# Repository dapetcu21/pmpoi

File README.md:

# PM Poi

> Visual Poi hardware project.

## Definitions

[Poi - performance art, Wikipedia page](https://en.wikipedia.org/wiki/Poi_(performance_art)#Glow_poi.2Fglowstringing)

It looks like this:

## About this project

This is my project for the MCU programming class from University.

## Hardware

Since this is a project for Uni, we had to use the provided ATMEGA324PA development [board](./hardware/pm2016.brd).

On top of it, I created an extension [board](./hardware/pmpoi.sch) with a shield-like form factor.

The main stars of the extension board are:

  * 8 RGB LEDs connected to the entirety of PORTB, PORTD and PORTA through a set of transitor array ICs. I could have used some PWM driver IC, but then where's all the fun? (To be read as: I didn't want to wait for the parts, so I just used what I could readily find at my local vendor.)

  * an MPU6050 gyro (on a GY-521 breakout board).

  * 3 buttons for good measure.

  * 3 AAA batteries to keep the board running.

Since this will spin freely in the air, I needed to make it sturdy, so I used screw mount dividers and no ribbon cables for the build.

Of course, most poi tehnique requires two poi, so I had to make two.

Attach this to a set of poi leashes and we're ready to dance.

### Caveats

Since I configured my bootloader to start when PD7 is pressed (sunk to GND) and I also connected PD7 to the input of the transistor array (which also pulled to GND, probably in a more stronger fashion than the 20K internal pull-up on PD7 protects against), I had to add a stronger pull-up resistor on that pin (3.3K).

Of course, since I also had to use PD2 and PD3 for the LEDs, plugging this into a computer won't do anything. But then if you want to program it, sometimes a reset is not be enough for your computer to pick it up. You might have to unplug the cable, wait a few seconds and plug it again. This happens because your computer's USB controller remembers that a non-compliant USB device was plugged into that port and decides to ignore it, even if you decide to send valid USB traffic at some point.

## Software

For the bootloader, I used [USBaspLoader](https://github.com/baerwolf/USBaspLoader) since it works via V-USB and plays nice with avrdude.

As a development environment, I just wrote a `Makefile` and a `.clang_complete` file to get autocomplete to work and built the whole thing in Atom.

### LED PWM

Since I have to drive 8 RGB LEDs (24 independent channels) in software PWM operation, I decided to use a novel approach:

Since PWM has to be fast, we have to keep our timer's ISR small.

I decided to use all the pins from 3 ports because it's easy to change them all at the same time. That's why, every time I would need to change the color of the LEDs, I would pre-calculate a render buffer with `B[i]`, the state of the each of the 3 ports at the time `i`. We can make `i` sweep from `0` to `15` and then loop around as the timer ticks.

For example, let's say I want to keep one of the LEDs at 25% brightness. I would first figure out what's the corresponding port and bit for the LED, then mark it as `1` in `B[0]`, `B[1]`, `B[2]`, `B[3]` and as `0` in `B[4- 15]`. This way, as the timer sweeps the render buffer, the LED will be lit 4 times out of 16.

Because modifying the render buffer during rendering might cause unexpected flickers, I decided to go with a double buffered approach. Every time I need to update the color of the LEDs, I fill in an off-screen render buffer, then mark it as ready for display. The ISR would then swap it with its current render buffer at the end of a `0 - 16` cycle (frame).

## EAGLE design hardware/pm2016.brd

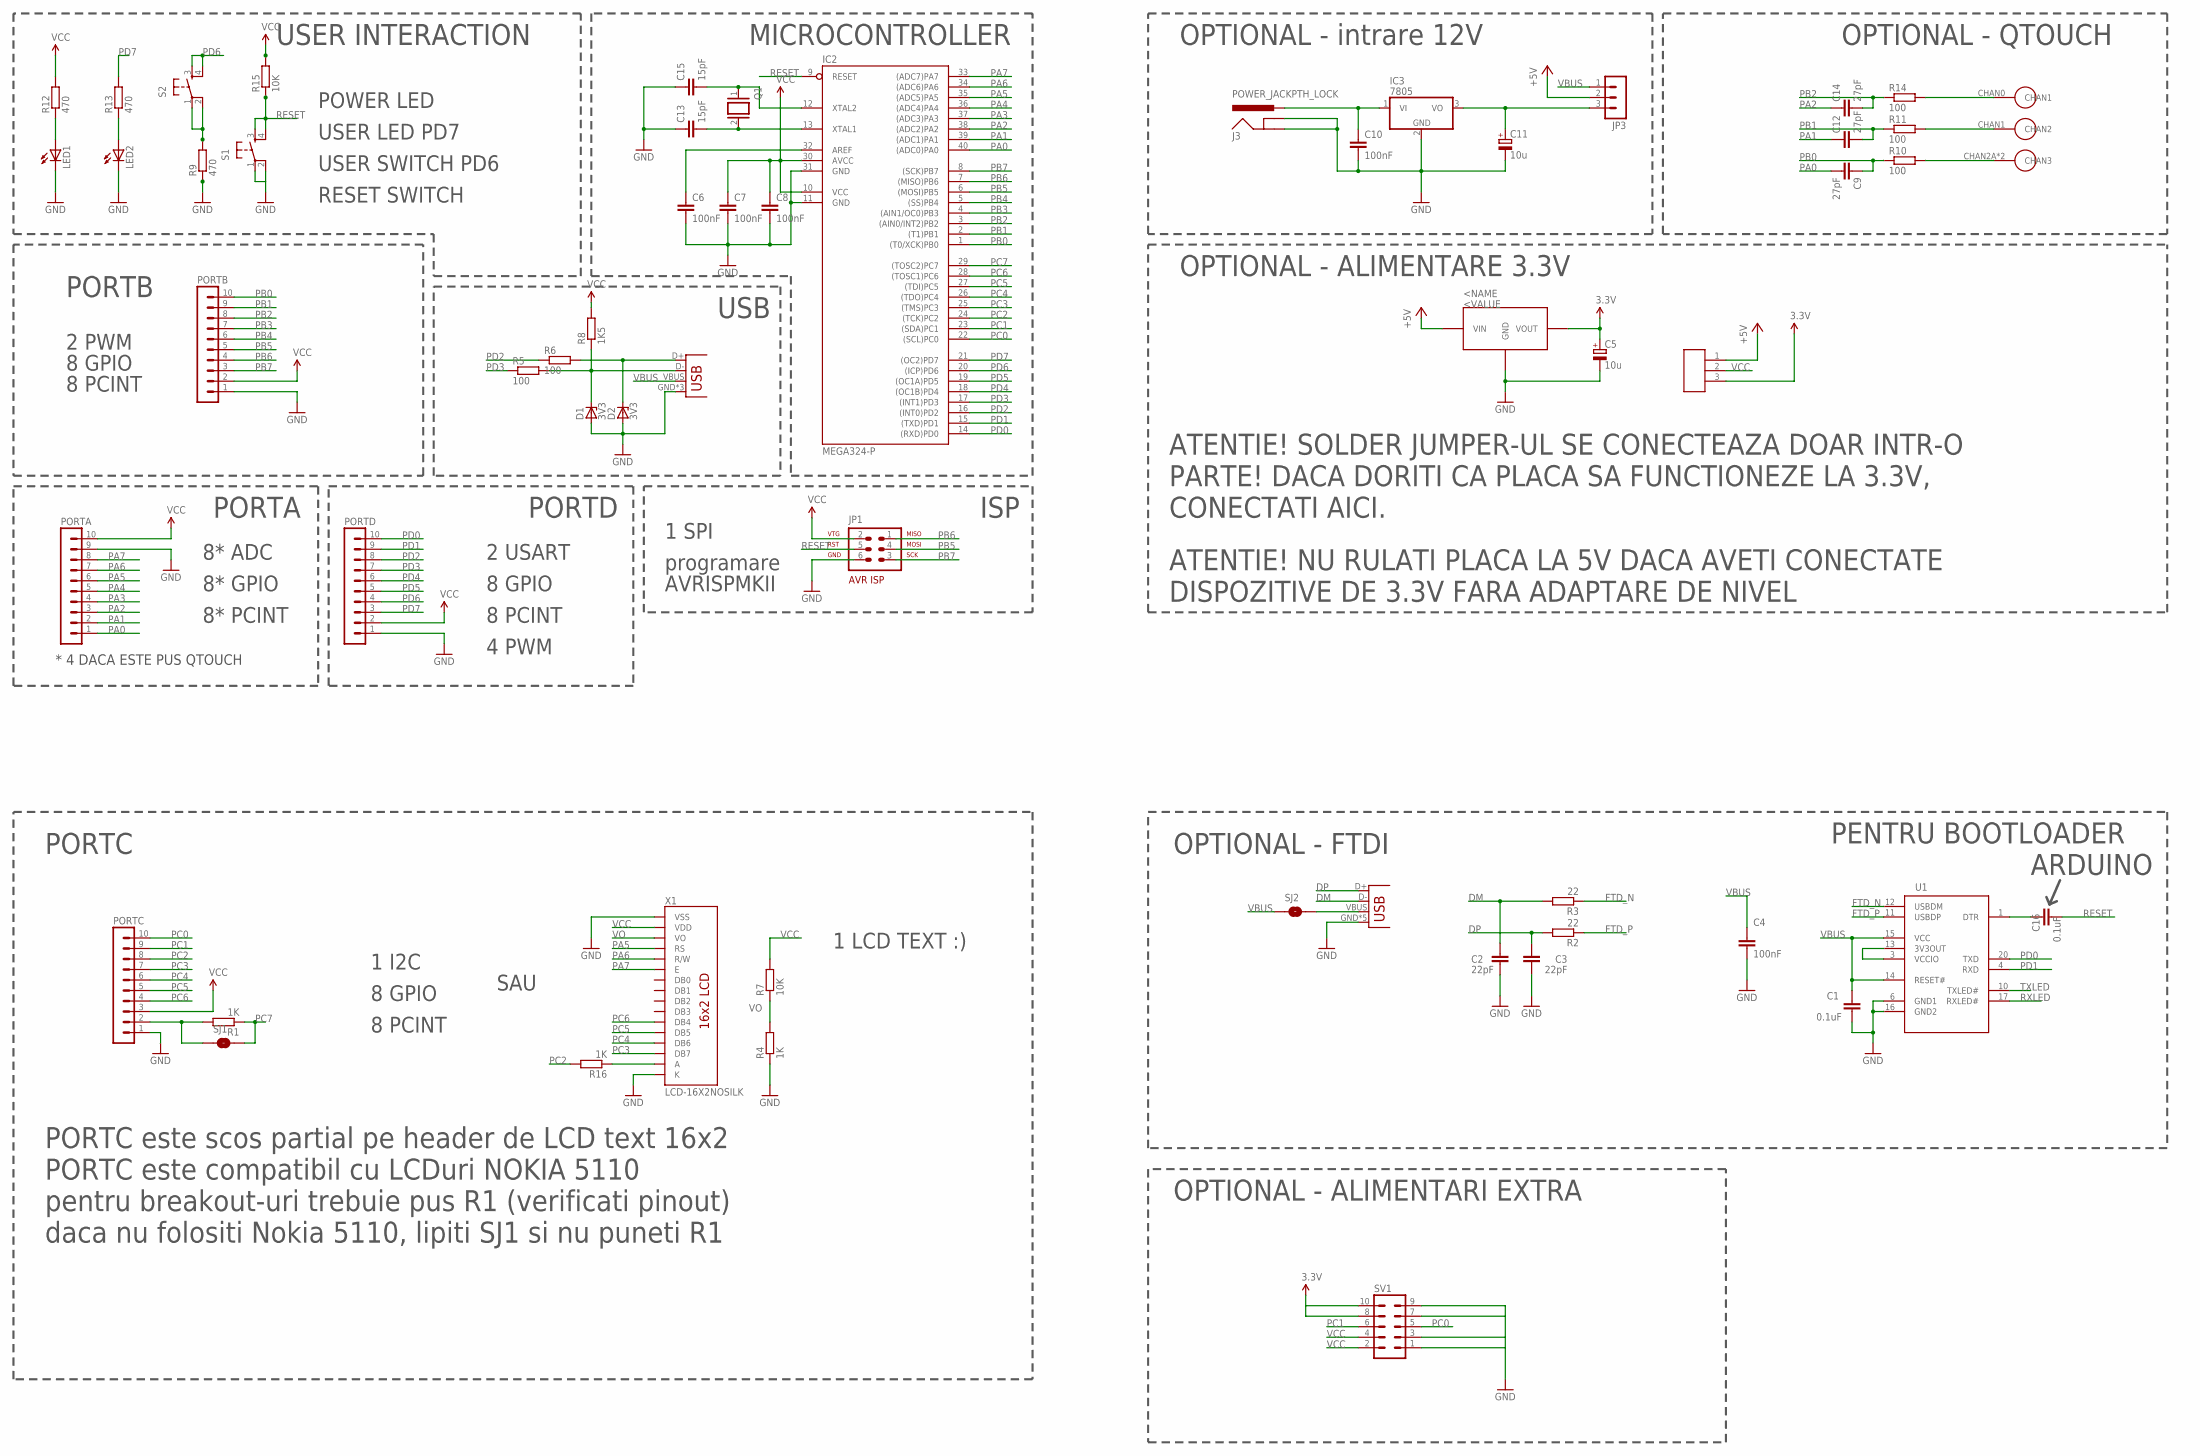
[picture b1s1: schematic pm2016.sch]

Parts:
C1, C16: 0.1uF; C0603
C2, C3: 22pF; C0603
C4: 100nF; C0603
C5, C11: 10u; E2,5-5
C6, C7, C8: 100nF; C025-025X050
C9, C12, C14: 27pF; C1206
C10: 100nF; C025-025X050@1
C13, C15: 15pF; C025-025X050
D1, D2: 3V3; DO34Z7
IC1: LE33; TO92
IC2: MEGA324-P; DIL40
IC3: 7805; TO22H_NOHOLE
J1: USB; ZX62D-B-5PA8
J2: USBPTH; USB-B-PTH
J3: POWER_JACKPTH_LOCK; POWER_JACK_PTH_LOCK
JP1: AVR-ISP-6
JP2: SJUMPER; SJUMPER_PACK
JP3: MA03-1
LED1, LED2: LED5MM
PORTA: MA10-1
PORTB: MA10-1
PORTC: MA10-1
PORTD: MA10-1
Q1: XTAL/S; QS
R1, R4, R16: 1K; 0204/7
R2, R3: 22; R0603
R5, R6: 100; 0204/7
R7, R15: 10K; 0204/7
R8: 1K5; 0204/7
R9, R12, R13: 470; 0204/7
R10, R11, R14: 100; M1206
S1, S2: TAC_SWITCHPTH; TACTILE-PTH
SJ1, SJ2: SOLDERJUMPERNC; SJ-NC
SV1: MA05-2
U1: FT231XS; SSOP20
U$1: QT_SLIDER
X1: LCD-16X2NOSILK; LCD-16X2_NOSILK

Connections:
3.3V: C5.+, IC1.1 (VOUT), JP2.3, SV1.8, SV1.10
+5V: IC1.3 (VIN), JP2.1, JP3.2
DM: C2.2, J1.D-, R3.2
DP: C3.2, J1.D+, R2.2
FTD_N: R3.1, U1.12 (USBDM)
FTD_P: R2.1, U1.11 (USBDP)
GND: C1.2, C2.1, C3.1, C4.2, C5.-, C6.2, C7.2, C8.2, C10.2, C11.-, C13.1, C15.1, D1.A, D2.A, IC1.2 (GND), IC2.11 (GND), IC2.31 (GND), IC3.2 (GND), J1.GND, J1.P$8 (GND), J1.P$9 (GND), J1.P$10 (GND), J1.P$11 (GND), J2.GND, J2.P$1 (GND), J2.P$2 (GND), J3.GND, J3.GNDBREAK, JP1.6, LED1.K (C), LED2.K (C), PORTA.9, PORTB.1, PORTC.1, PORTD.1, R4.1, R9.1, S1.1, S1.2, SV1.1, SV1.3, SV1.7, SV1.9, U1.6 (GND1), U1.16 (GND2), X1.1 (VSS), X1.16 (K)
unnamed: LED2.A, R13.1
unnamed: LED1.A, R12.1
unnamed: PORTC.2, R1.2, SJ1.1
unnamed: J1.VBUS, SJ2.2
unnamed: R14.2, U$1.CHAN0 (CHAN1)
unnamed: R11.2, U$1.CHAN1 (CHAN2)
unnamed: R10.2, U$1.CHAN2A (CHAN3), U$1.CHAN2B (CHAN3)
unnamed: R16.1, X1.15 (A)
unnamed: C16.1, U1.1 (DTR)
unnamed: U1.3 (VCCIO), U1.13 (3V3OUT)
unnamed: D2.C, J2.D+, R6.2
unnamed: D1.C, J2.D-, R5.2, R8.1
unnamed: C10.1, IC3.1 (VI), J3.PWR
unnamed: R9.2, S2.1, S2.2
unnamed: C11.+, IC3.3 (VO), JP3.3
unnamed: C6.1, IC2.32 (AREF)
unnamed: C13.2, IC2.13 (XTAL1), Q1.2
unnamed: C15.2, IC2.12 (XTAL2), Q1.1
PA0: C9.2, IC2.40 ((ADC0)PA0), PORTA.1
PA1: C12.1, IC2.39 ((ADC1)PA1), PORTA.2
PA2: C14.1, IC2.38 ((ADC2)PA2), PORTA.3
PA3: IC2.37 ((ADC3)PA3), PORTA.4
PA4: IC2.36 ((ADC4)PA4), PORTA.5
PA5: IC2.35 ((ADC5)PA5), PORTA.6, X1.4 (RS)
PA6: IC2.34 ((ADC6)PA6), PORTA.7, X1.5 (R/W)
PA7: IC2.33 ((ADC7)PA7), PORTA.8, X1.6 (E)
PB0: C9.1, IC2.1 ((T0/XCK)PB0), PORTB.10, R10.1
PB1: C12.2, IC2.2 ((T1)PB1), PORTB.9, R11.1
PB2: C14.2, IC2.3 ((AIN0/INT2)PB2), PORTB.8, R14.1
PB3: IC2.4 ((AIN1/OC0)PB3), PORTB.7
PB4: IC2.5 ((SS)PB4), PORTB.6
PB5: IC2.6 ((MOSI)PB5), JP1.4, PORTB.5
PB6: IC2.7 ((MISO)PB6), JP1.1, PORTB.4
PB7: IC2.8 ((SCK)PB7), JP1.3, PORTB.3
PC0: IC2.22 ((SCL)PC0), PORTC.10, SV1.5
PC1: IC2.23 ((SDA)PC1), PORTC.9, SV1.6
PC2: IC2.24 ((TCK)PC2), PORTC.8, R16.2
PC3: IC2.25 ((TMS)PC3), PORTC.7, X1.14 (DB7)
PC4: IC2.26 ((TDO)PC4), PORTC.6, X1.13 (DB6)
PC5: IC2.27 ((TDI)PC5), PORTC.5, X1.12 (DB5)
PC6: IC2.28 ((TOSC1)PC6), PORTC.4, X1.11 (DB4)
PC7: IC2.29 ((TOSC2)PC7), R1.1, SJ1.2
PD0: IC2.14 ((RXD)PD0), PORTD.10, U1.20 (TXD)
PD1: IC2.15 ((TXD)PD1), PORTD.9, U1.4 (RXD)
PD2: IC2.16 ((INT0)PD2), PORTD.8, R6.1
PD3: IC2.17 ((INT1)PD3), PORTD.7, R5.1
PD4: IC2.18 ((OC1B)PD4), PORTD.6
PD5: IC2.19 ((OC1A)PD5), PORTD.5
PD6: IC2.20 ((ICP)PD6), PORTD.4, S2.3, S2.4
PD7: IC2.21 ((OC2)PD7), PORTD.3, R13.2
RESET: C16.2, IC2.9 (RESET), JP1.5, R15.1, S1.3, S1.4
RXLED: U1.17 (RXLED#)
TXLED: U1.10 (TXLED#)
VBUS: C1.1, C4.1, J2.VBUS, JP3.1, SJ2.1, U1.14 (RESET#), U1.15 (VCC)
VCC: C7.1, C8.1, IC2.10 (VCC), IC2.30 (AVCC), JP1.2, JP2.2, PORTA.10, PORTB.2, PORTC.3, PORTD.2, R7.2, R8.2, R12.2, R15.2, SV1.2, SV1.4, X1.2 (VDD)
VO: R4.2, R7.1, X1.3 (VO)

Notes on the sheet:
8* ADC
8* GPIO
8* PCINT
* 4 DACA ESTE PUS QTOUCH
1 I2C
8 GPIO
8 PCINT
2 USART
4 PWM
1 SPI
programare
AVRISPMKII
PORTA
PORTC
PORTD
USB
ISP
POWER LED
USER LED PD7
USER SWITCH PD6
RESET SWITCH
USER INTERACTION
MICROCONTROLLER
OPTIONAL - intrare 12V
OPTIONAL - QTOUCH
OPTIONAL - ALIMENTARE 3.3V
ATENTIE! SOLDER JUMPER-UL SE CONECTEAZA DOAR INTR-O
PARTE! DACA DORITI CA PLACA SA FUNCTIONEZE LA 3.3V,
CONECTATI AICI.
ATENTIE! NU RULATI PLACA LA 5V DACA AVETI CONECTATE
DISPOZITIVE DE 3.3V FARA ADAPTARE DE NIVEL
PORTB
2 PWM
1 LCD TEXT :)
SAU
OPTIONAL - FTDI
PORTC este compatibil cu LCDuri NOKIA 5110
pentru breakout-uri trebuie pus R1 (verificati pinout)
daca nu folositi Nokia 5110, lipiti SJ1 si nu puneti R1
PORTC este scos partial pe header de LCD text 16x2

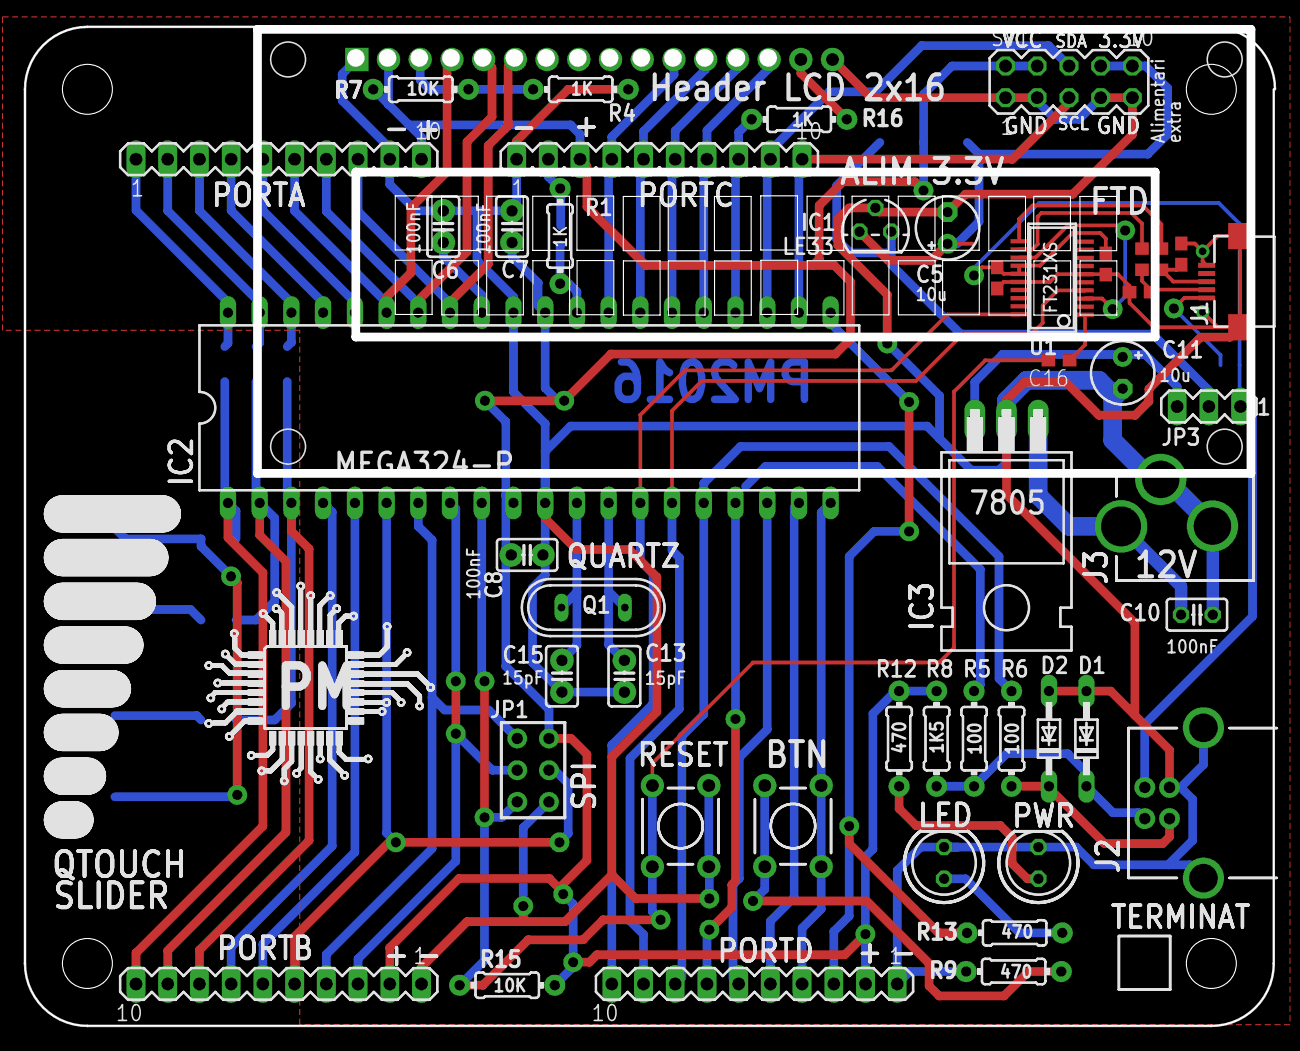
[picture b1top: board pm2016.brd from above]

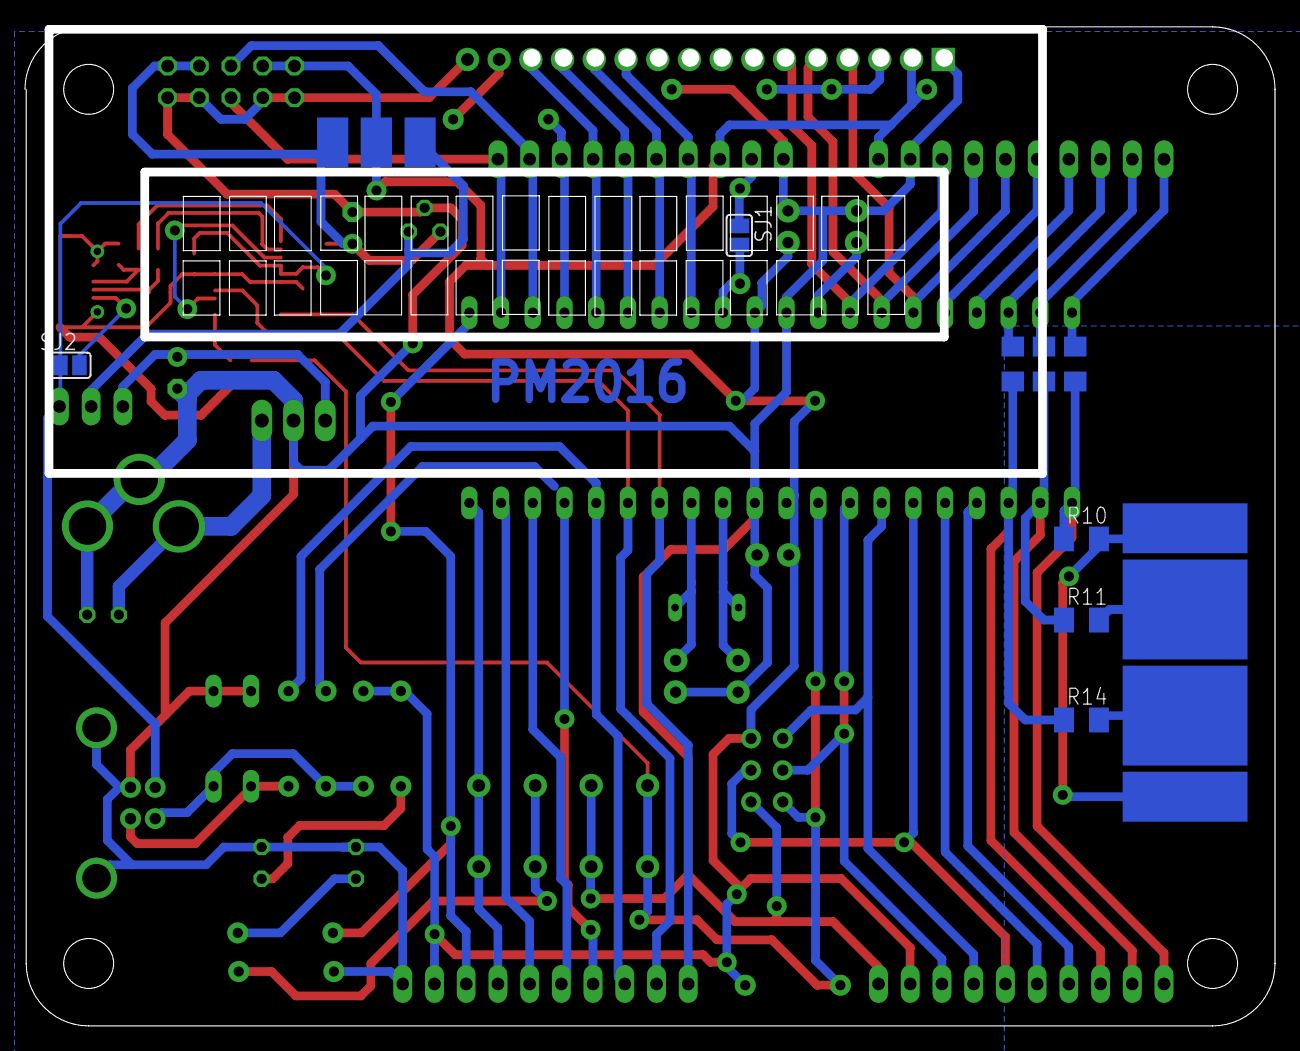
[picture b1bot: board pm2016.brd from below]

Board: 2 copper layers, 100.1 x 80.0 mm, 58 parts (10 on the bottom side), 61 nets.

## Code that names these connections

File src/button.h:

#pragma once

#include <avr/io.h>
#include <avr/interrupt.h>
#include <stdint.h>

#define BUTTON_GYRO_INT PC2
#define BUTTON_A PC3
#define BUTTON_RIGHT PC4
#define BUTTON_LEFT PC5

#define BUTTON_MIN PC2
#define BUTTON_MAX PC5

#define BUTTON_HYST_MIN PC3
#define BUTTON_HYST_MAX PC5

#define BUTTON_MASK ((1 << BUTTON_GYRO_INT) | (1 << BUTTON_A) | (1 << BUTTON_LEFT) | (1 << BUTTON_RIGHT))
#define BUTTON_HYSTERESIS_MASK ((1 << BUTTON_A) | (1 << BUTTON_LEFT) | (1 << BUTTON_RIGHT))

#define BUTTON_DDR DDRC
#define BUTTON_PORT PORTC
#define BUTTON_PIN PINC
#define BUTTON_PCICR_BIT PCIE2
#define BUTTON_PCMSK PCMSK2
#define BUTTON_VECT PCINT2_vect

void buttonInit();
void buttonCheckChange();
void buttonOnPress(uint8_t button);
void buttonOnRelease(uint8_t button);

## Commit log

2016-04-13 Working solid color PWM
2016-04-13 Create readme.md with wiki link and demo image
2016-04-13 Implement byte and half byte buffer rendering
2016-04-13 Fix README link to poi.gif
2016-04-13 Rename readme to caps. Part 1
2016-04-13 Rename readme to caps. Part 2
2016-04-13 Wrong gif branch
2016-04-13 Try local reference to poi.gif
2016-04-13 Move poi.gif to docs/img
2016-04-13 Add detailed README
2016-04-13 Improve wording for sweeping explaination
2016-04-14 Add button interrupts with hysterisis and time counter
2016-04-14 Implement gyro interrupt
2016-04-15 Split OBJFILES on multiple lines in Makefile
2016-04-23 Update schematic with PD7 pull-up
2016-04-23 Add diagram
2016-05-10 Generate pattern sources from images
2016-05-10 Change structure of pattern header
2016-05-10 Add generated pattern headers in .gitignore
2016-05-10 Add 4 patterns
2016-05-11 Architect pattern system
2016-05-11 Indent with 4 spaces
2016-05-12 Implement image POV
2016-05-12 Implement slow spinning mode and menu indicator
2016-05-13 Smooth out menu indicator transitions
2016-05-17 Store selected pattern in EEPROM
2016-05-17 Add saw pattern

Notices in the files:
parts and their libraries:
SparkFun-Connectors: Licensing: CC v3.0 Share-Alike You are welcome to use this library for commercial purposes.
